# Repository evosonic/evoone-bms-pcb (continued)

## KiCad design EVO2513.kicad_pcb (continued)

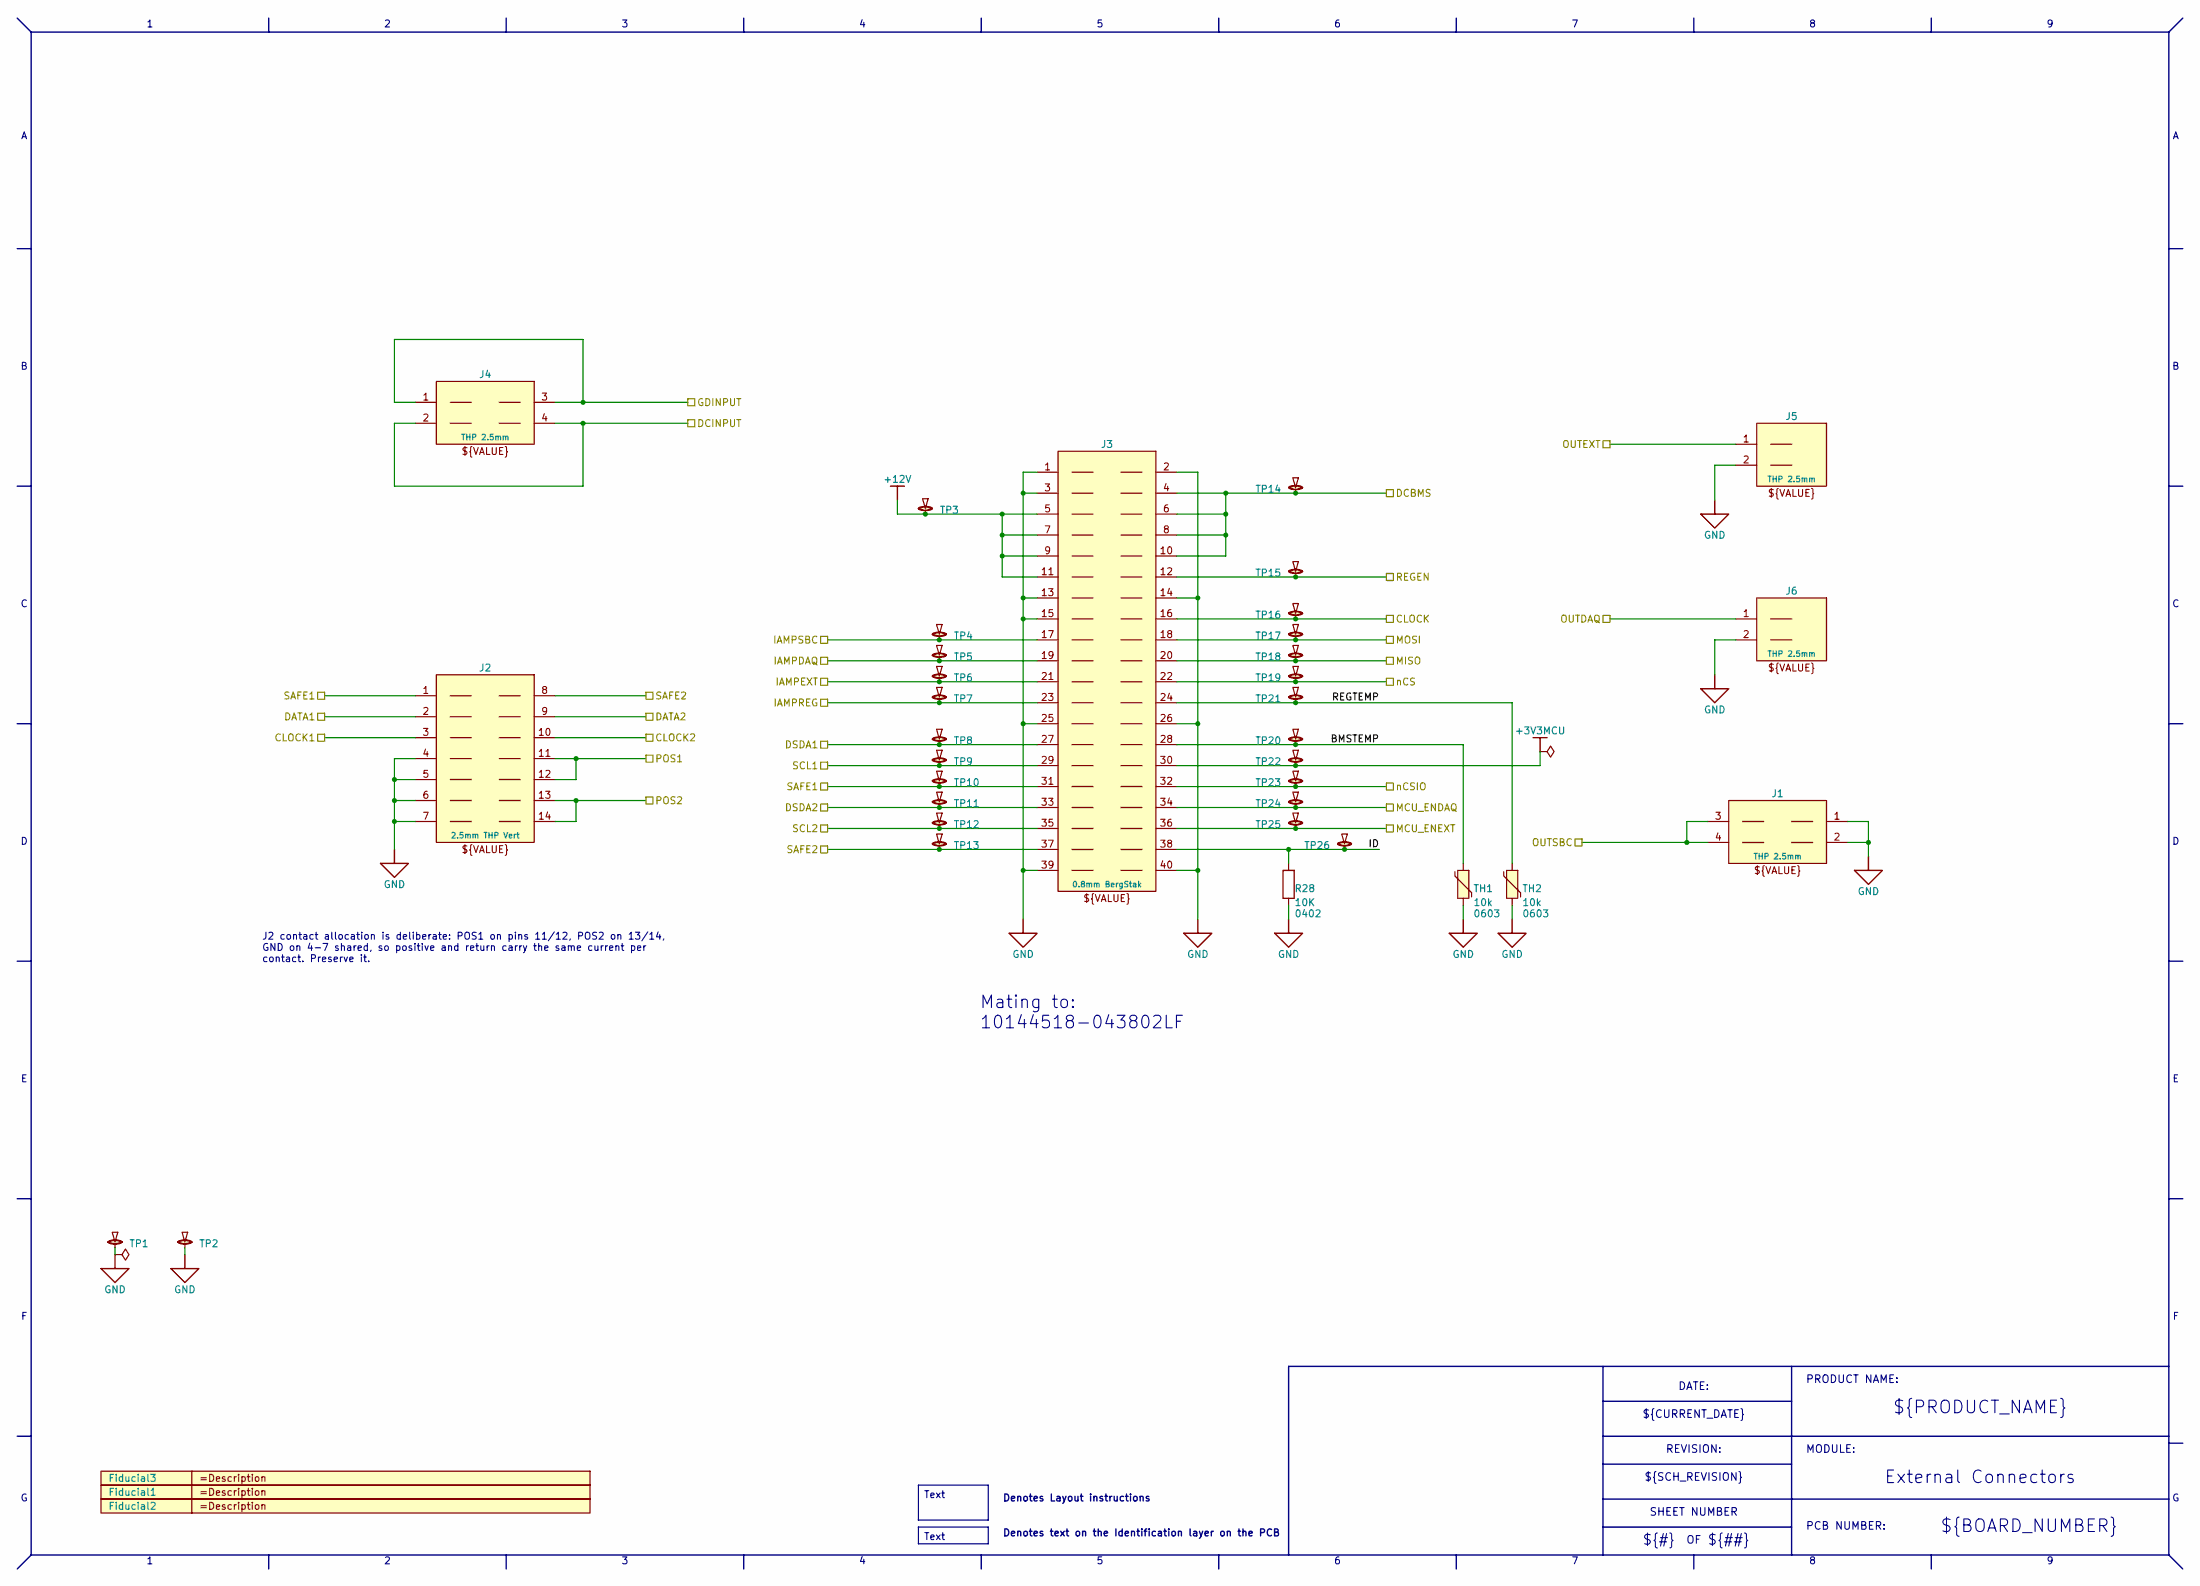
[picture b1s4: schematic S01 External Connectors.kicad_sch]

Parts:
Fiducial1, Fiducial2, Fiducial3: Fiducial; Fiducial-50
J1: 1053101204; Connector Molex 105310xx04 4POS 2.5mm THP; MANUFACTURER_PN 1053101204
J2: 1053101114; CONNECTOR MOLEX 1053101114 2.5MM THP; MANUFACTURER_PN 1053101114
J3: 10144517-043802LF; Connector Amphenol BergStak 10144517-043802LF 40-Pin Recept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; MANUFACTURER_PN 10144517-043802LF
J4: 1053102204; Connector Molex 105310xx04 4POS 2.5mm THP; MANUFACTURER_PN 1053102204
J5, J6: 1053091102; CONNECTOR MOLEX 1053091102 2POS 2.5MM THP; MANUFACTURER_PN 1053091102
R28: 10K; R_0402_1005Metric; MANUFACTURER_PN RC0402FR-0710KL
TH1, TH2: 10k; R_0603_1608Metric; MANUFACTURER_PN NCU18XH103E6SRB
TP1, TP2, TP3, TP4, TP5, TP6, TP7, TP8, TP9, TP10, TP11, TP12, TP13, TP14, TP15, TP16, TP17, TP18, TP19, TP20, TP21, TP22, TP23, TP24, TP25, TP26: POGO-1; TEST PIN 1-25mm SMD Pad (POGO-1)

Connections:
+3V3MCU: J3.30 (I/O), TP22.1 (1_1); also elsewhere on the board
+12V: J3.5 (I/O), J3.7 (I/O), J3.9 (I/O), J3.11 (I/O), TP3.1 (1_1); also elsewhere on the board
/CLOCK: J3.16 (I/O), TP16.1 (1_1); also elsewhere on the board
/CLOCK1: J2.3 (I/O); also elsewhere on the board
/CLOCK2: J2.10 (I/O); also elsewhere on the board
/DATA1: J2.2 (I/O); also elsewhere on the board
/DATA2: J2.9 (I/O); also elsewhere on the board
/DCBMS: J3.4 (I/O), J3.6 (I/O), J3.8 (I/O), J3.10 (I/O), TP14.1 (1_1); also elsewhere on the board
/DCINPUT: J4.2 (I/O), J4.4 (I/O); also elsewhere on the board
/DSDA1: J3.27 (I/O), TP8.1 (1_1); also elsewhere on the board
/DSDA2: J3.33 (I/O), TP11.1 (1_1); also elsewhere on the board
/GDINPUT: J4.1 (I/O), J4.3 (I/O); also elsewhere on the board
/IAMPDAQ: J3.19 (I/O), TP5.1 (1_1); also elsewhere on the board
/IAMPEXT: J3.21 (I/O), TP6.1 (1_1); also elsewhere on the board
/IAMPREG: J3.23 (I/O), TP7.1 (1_1); also elsewhere on the board
/IAMPSBC: J3.17 (I/O), TP4.1 (1_1); also elsewhere on the board
/MCU_ENDAQ: J3.34 (I/O), TP24.1 (1_1); also elsewhere on the board
/MCU_ENEXT: J3.36 (I/O), TP25.1 (1_1); also elsewhere on the board
/MISO: J3.20 (I/O), TP18.1 (1_1); also elsewhere on the board
/MOSI: J3.18 (I/O), TP17.1 (1_1); also elsewhere on the board
/OUTDAQ: J6.1 (I/O); also elsewhere on the board
/OUTEXT: J5.1 (I/O); also elsewhere on the board
/OUTSBC: J1.3 (I/O), J1.4 (I/O); also elsewhere on the board
/POS1: J2.11 (I/O), J2.12 (I/O); also elsewhere on the board
/POS2: J2.13 (I/O), J2.14 (I/O); also elsewhere on the board
/REGEN: J3.12 (I/O), TP15.1 (1_1); also elsewhere on the board
/S01 External Connectors/BMSTEMP: J3.28 (I/O), TH1.2, TP20.1 (1_1)
/S01 External Connectors/ID: J3.38 (I/O), R28.2, TP26.1 (1_1)
/S01 External Connectors/REGTEMP: J3.24 (I/O), TH2.2, TP21.1 (1_1)
/SAFE1: J2.1 (I/O), J3.31 (I/O), TP10.1 (1_1); also elsewhere on the board
/SAFE2: J2.8 (I/O), J3.37 (I/O), TP13.1 (1_1); also elsewhere on the board
/SCL1: J3.29 (I/O), TP9.1 (1_1); also elsewhere on the board
/SCL2: J3.35 (I/O), TP12.1 (1_1); also elsewhere on the board
/nCS: J3.22 (I/O), TP19.1 (1_1); also elsewhere on the board
/nCSIO: J3.32 (I/O), TP23.1 (1_1); also elsewhere on the board
GND: J1.1 (I/O), J1.2 (I/O), J2.4 (I/O), J2.5 (I/O), J2.6 (I/O), J2.7 (I/O), J3.1 (I/O), J3.2 (I/O), J3.3 (I/O), J3.13 (I/O), J3.14 (I/O), J3.15 (I/O), J3.25 (I/O), J3.26 (I/O), J3.39 (I/O), J3.40 (I/O), J5.2 (I/O), J6.2 (I/O), R28.1, TH1.1, TH2.1, TP1.1 (1_1), TP2.1 (1_1); also elsewhere on the board

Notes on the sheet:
Denotes Layout instructions
PCB NUMBER:
${BOARD_NUMBER}
REVISION:
${#}
PRODUCT NAME:
J2 contact allocation is deliberate: POS1 on pins 11/12, POS2 on 13/14, GND on 4-7 shared, so positive and return carry the same current per contact. Preserve it.
${PRODUCT_NAME}
SHEET NUMBER
${SCH_REVISION}
MODULE:
DATE:
External Connectors
${CURRENT_DATE}
${##}
Denotes text on the Identification layer on the PCB
Mating to: 10144518-043802LF
Text

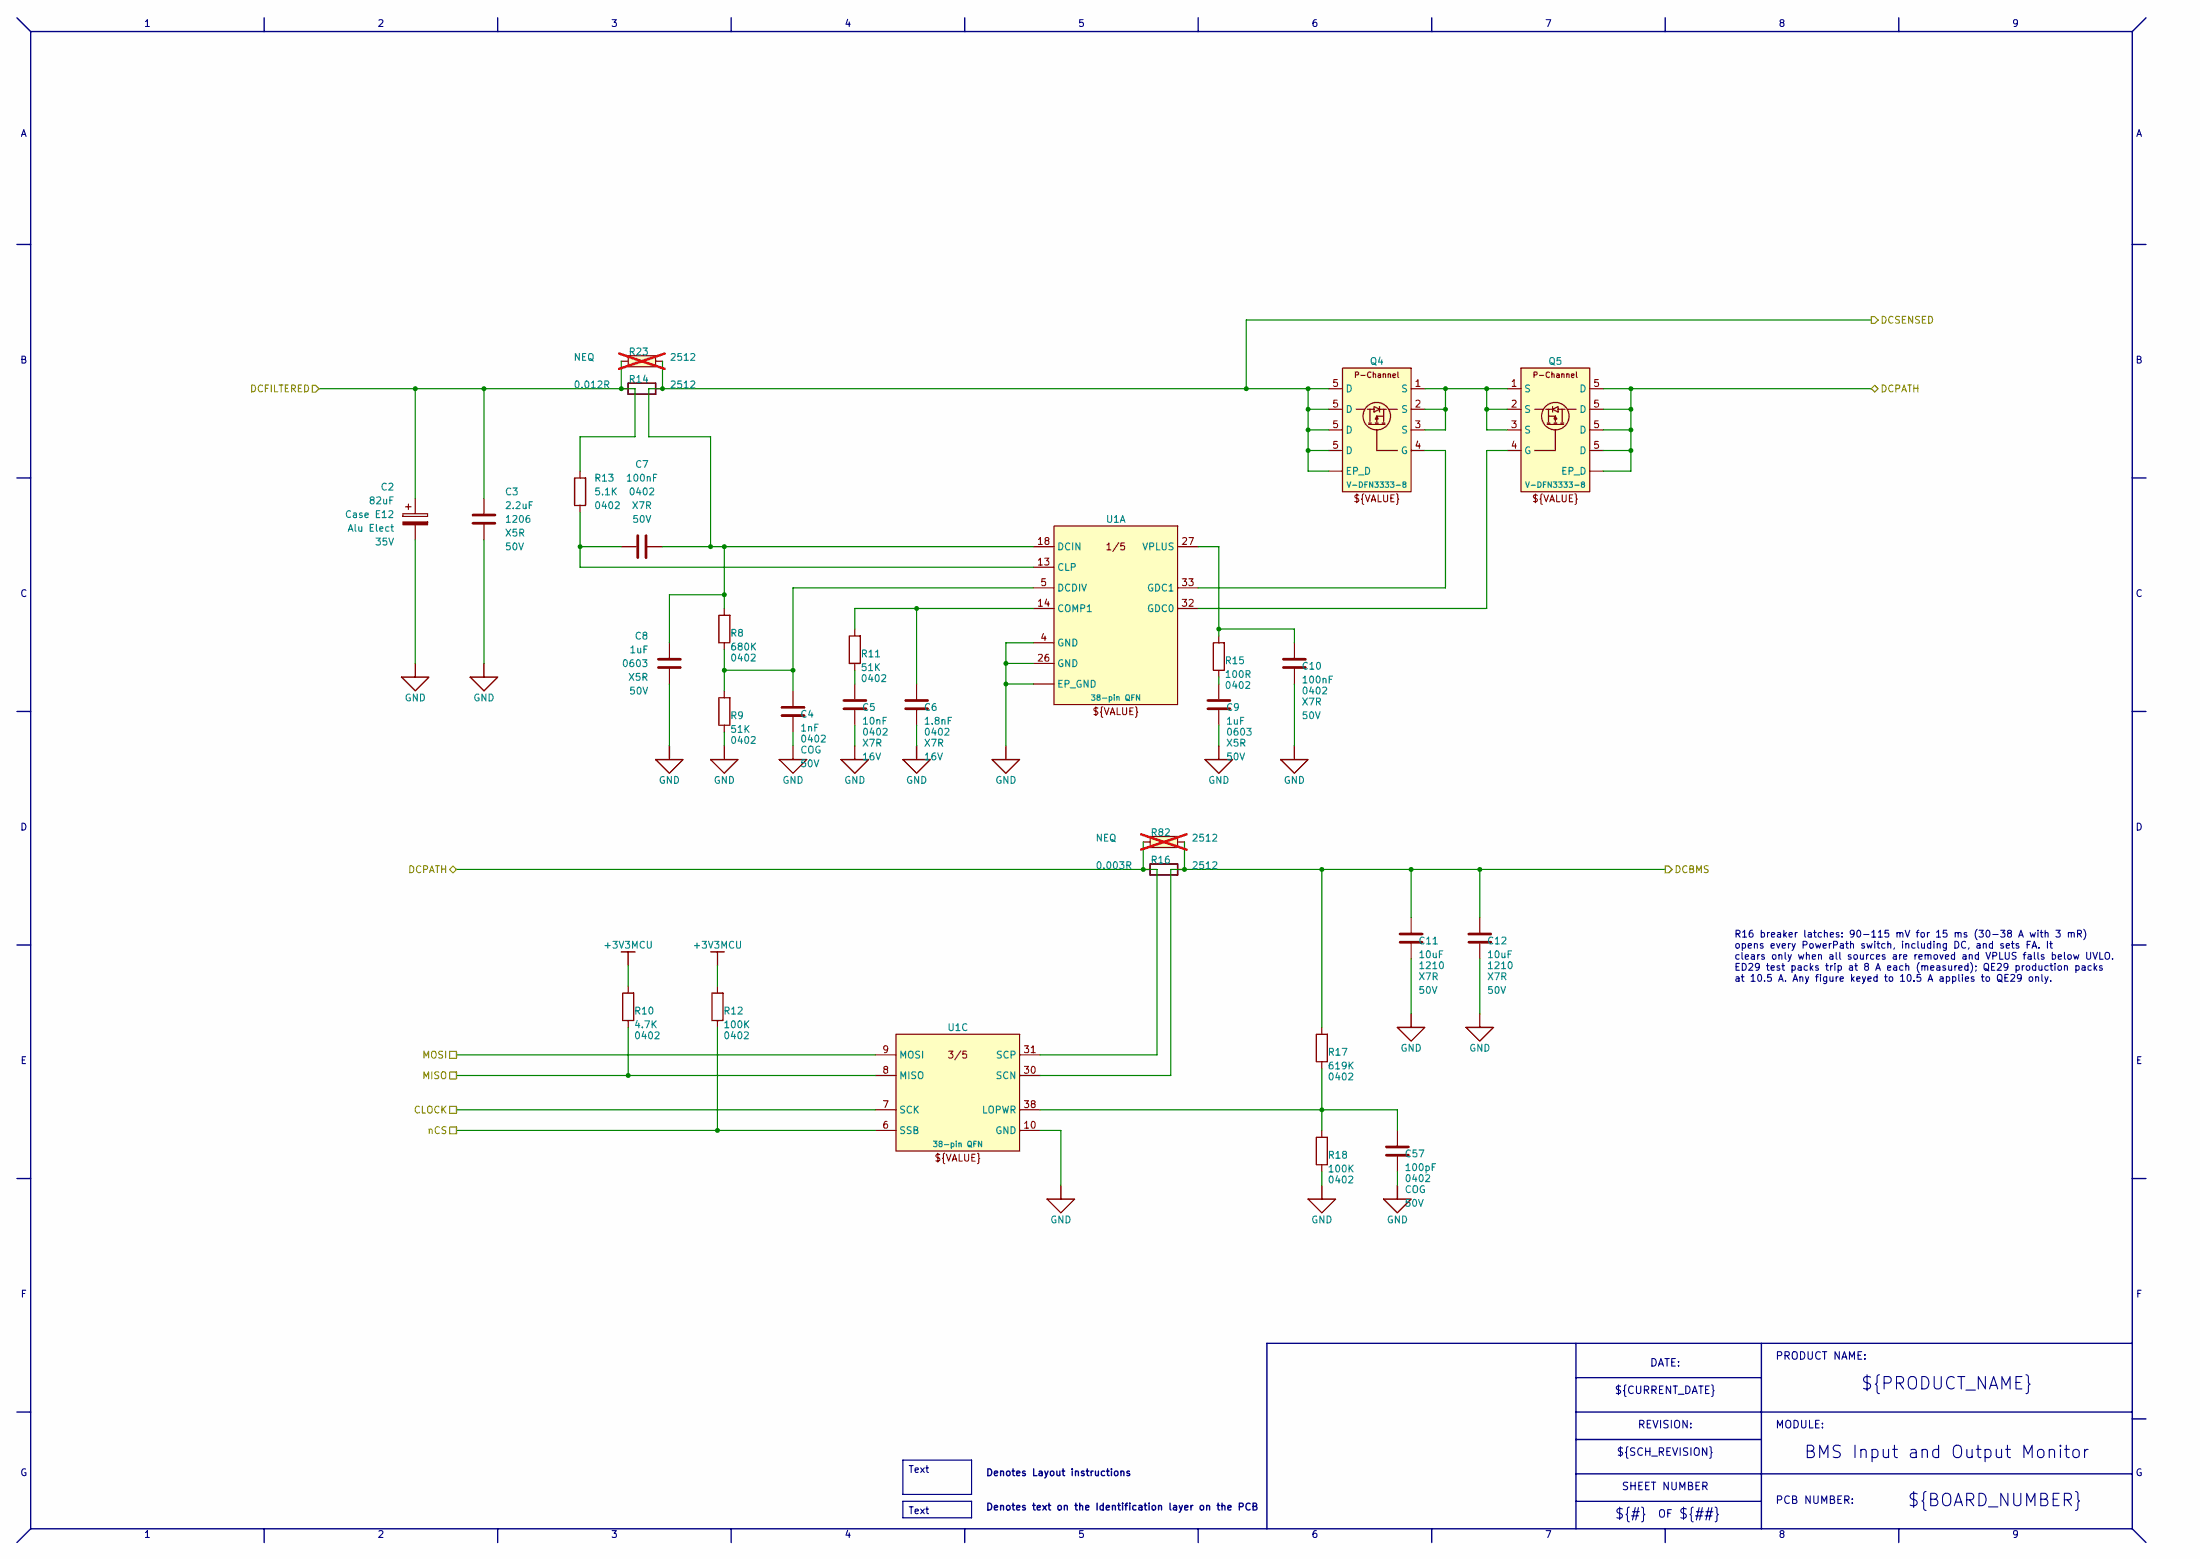
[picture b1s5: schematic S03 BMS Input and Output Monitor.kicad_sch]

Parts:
C2: 82uF; CAP Panasonic CASE-E12; VOLTAGE 35V; MANUFACTURER_PN 35SVPF82M
C3: 2.2uF; C_1206_3216Metric; VOLTAGE 50V; MANUFACTURER_PN CC1206KKX5R9BB225
C4: 1nF; C_0402_1005Metric; VOLTAGE 50V; MANUFACTURER_PN AC0402JRNPO9BN102
C5: 10nF; C_0402_1005Metric; VOLTAGE 16V; MANUFACTURER_PN GRM155R71C103KA01D
C6: 1.8nF; C_0402_1005Metric; VOLTAGE 16V; MANUFACTURER_PN CC0402KRX7R9BB182
C7, C10: 100nF; C_0402_1005Metric; VOLTAGE 50V; MANUFACTURER_PN CC0402KPX7R9BB104
C8, C9: 1uF; C_0603_1608Metric; VOLTAGE 50V; MANUFACTURER_PN CL10A105KB8NNNC
C11, C12: 10uF; C_1210_3225Metric; VOLTAGE 50V; MANUFACTURER_PN UMK325AB7106KMHP
C57: 100pF; C_0402_1005Metric; VOLTAGE 50V; MANUFACTURER_PN CC0402JRNPO9BN101
Q4, Q5: DMP3007SCG-13; Diodes_PowerDI3333-8; MANUFACTURER_PN DMP3007SCG-13
R8: 680K; R_0402_1005Metric; MANUFACTURER_PN RC0402FR-07680KL
R9, R11: 51K; R_0402_1005Metric; MANUFACTURER_PN RC0402FR-0751KL
R10: 4.7K; R_0402_1005Metric; MANUFACTURER_PN RC0402FR-134K7L
R12, R18: 100K; R_0402_1005Metric; MANUFACTURER_PN RC0402FR-07100KL
R13: 5.1K; R_0402_1005Metric; MANUFACTURER_PN RC0402FR-075K1L
R14: 0.012R; R_2512_6332Metric; MANUFACTURER_PN PA2512FKE7W0R012E
R15: 100R; R_0402_1005Metric; MANUFACTURER_PN RC0402FR-07100RL
R16: 0.003R; R_2512_6332Metric; MANUFACTURER_PN CRE2512-FZ-R003E-3
R17: 619K; R_0402_1005Metric; MANUFACTURER_PN RC0402FR-07619KL
R23, R82: NEQ; R_2512_6332Metric; MANUFACTURER_PN Res 2512; not fitted
U1: LTC1960; QFN B5x7 P0-5 38-Pin EP; MANUFACTURER_PN LTC1960CUHF#PBF

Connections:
+3V3MCU: R10.2, R12.2; also elsewhere on the board
/CLOCK: U1.7 (SCK); also elsewhere on the board
/DCBMS: C11.2, C12.2, R16.2, R17.2, R82.2, U1.30 (SCN); also elsewhere on the board
/DCFILTERED: C2.1, C3.2, R13.2, R14.1, R23.1; also elsewhere on the board
/DCPATH: Q5.5 (EP_D), R16.1, R82.1, U1.31 (SCP); also elsewhere on the board
/DCSENSED: C7.2, C8.2, Q4.5 (EP_D), R8.2, R14.2, R23.2, U1.18 (DCIN); also elsewhere on the board
/MISO: R10.1, U1.8 (MISO); also elsewhere on the board
/MOSI: U1.9 (MOSI); also elsewhere on the board
/nCS: R12.1, U1.6 (SSB); also elsewhere on the board
GND: C2.2, C3.1, C4.1, C5.1, C6.1, C8.1, C9.1, C10.1, C11.1, C12.1, C57.1, R9.1, R18.1, U1.4 (GND), U1.10 (GND), U1.26 (GND), U1.39 (EP_GND); also elsewhere on the board
unnamed: C5.2, R11.1
unnamed: C9.2, R15.1
unnamed: Q4.4 (G), U1.33 (GDC1)
unnamed: Q4.1 (S), Q4.2 (S), Q4.3 (S), Q5.1 (S), Q5.2 (S), Q5.3 (S)
unnamed: Q5.4 (G), U1.32 (GDC0)
unnamed: C7.1, R13.1, U1.13 (CLP)
unnamed: C6.2, R11.2, U1.14 (COMP1)
unnamed: C4.2, R8.1, R9.2, U1.5 (DCDIV)
unnamed: C10.2, R15.2, U1.27 (VPLUS)
unnamed: C57.2, R17.1, R18.2, U1.38 (LOPWR)

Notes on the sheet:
${#}
PCB NUMBER:
SHEET NUMBER
MODULE:
${BOARD_NUMBER}
DATE:
${PRODUCT_NAME}
R16 breaker latches: 90-115 mV for 15 ms (30-38 A with 3 mR) opens every PowerPath switch, including DC, and sets FA. It clears only when all sources are removed and VPLUS falls below UVLO. ED29 test packs trip at 8 A each (measured); QE29 production packs at 10.5 A. Any figure keyed to 10.5 A appl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
${##}
Denotes text on the Identification layer on the PCB
PRODUCT NAME:
REVISION:
BMS Input and Output Monitor
Denotes Layout instructions
${CURRENT_DATE}
${SCH_REVISION}
Text

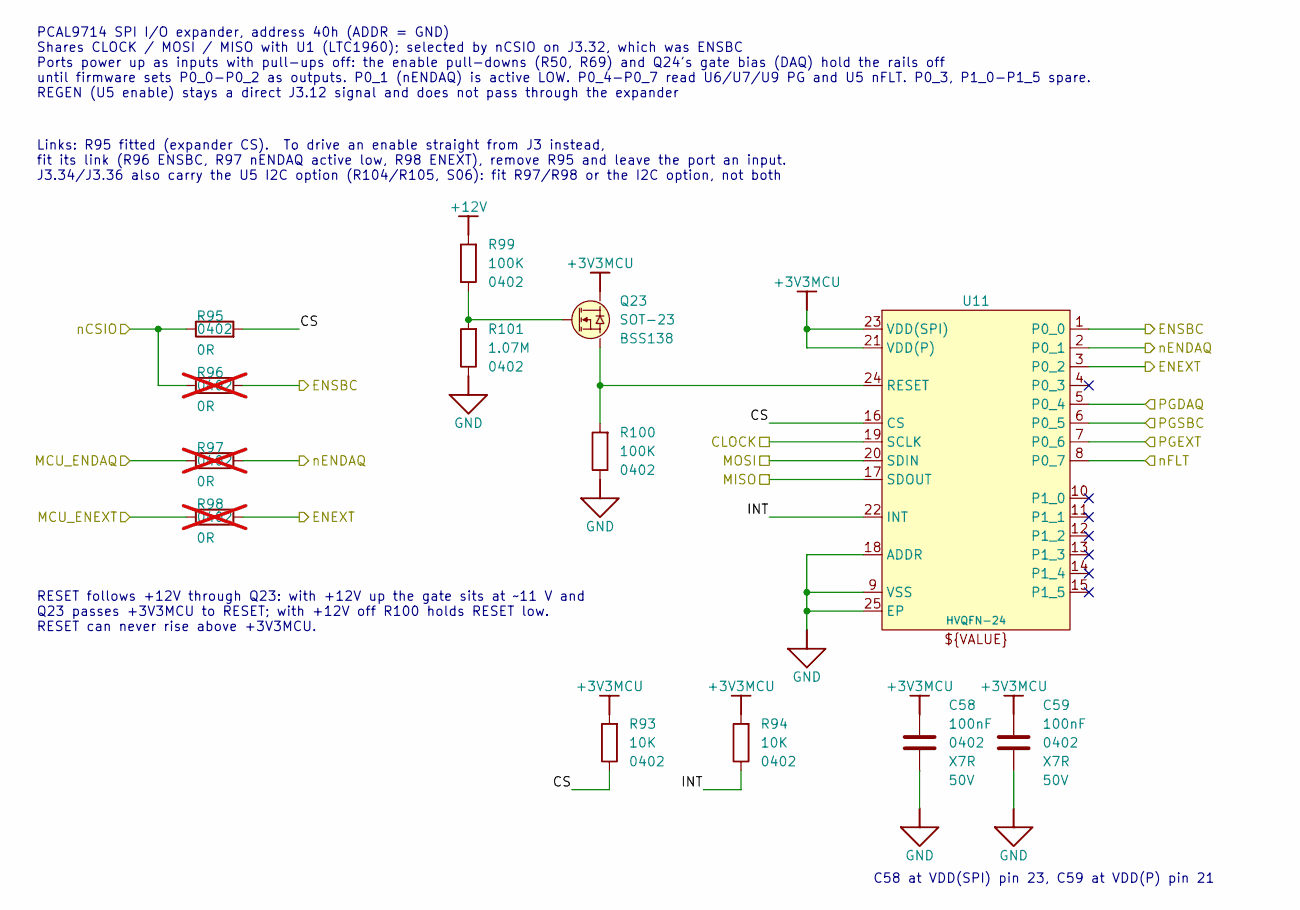
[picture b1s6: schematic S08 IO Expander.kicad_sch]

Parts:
C58, C59: 100nF; C_0402_1005Metric; VOLTAGE 50V; MANUFACTURER_PN CC0402KPX7R9BB104
Q23: BSS138; SOT-23; MANUFACTURER_PN BSS138
R93, R94: 10K; R_0402_1005Metric; MANUFACTURER_PN RC0402FR-0710KL
R95: 0R; R_0402_1005Metric; MANUFACTURER_PN RC0402JR-070RL
R96, R97, R98: 0R; R_0402_1005Metric; MANUFACTURER_PN RC0402JR-070RL; not fitted
R99, R100: 100K; R_0402_1005Metric; MANUFACTURER_PN RC0402FR-07100KL
R101: 1.07M; R_0402_1005Metric; MANUFACTURER_PN RC0402FR-071M07L
U11: PCAL9714; HVQFN-24-1EP_4x4mm_P0.5mm_EP2.6x2.6mm; MANUFACTURER_PN PCAL9714HNMP

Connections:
+3V3MCU: C58.2, C59.2, Q23.3 (D), R93.2, R94.2, U11.21 (VDD(P)), U11.23 (VDD(SPI)); also elsewhere on the board
+12V: R99.2; also elsewhere on the board
/CLOCK: U11.19 (SCLK); also elsewhere on the board
/ENEXT: R98.2, U11.3 (P0_2); also elsewhere on the board
/ENSBC: R96.2, U11.1 (P0_0); also elsewhere on the board
/MCU_ENDAQ: R97.1; also elsewhere on the board
/MCU_ENEXT: R98.1; also elsewhere on the board
/MISO: U11.17 (SDOUT); also elsewhere on the board
/MOSI: U11.20 (SDIN); also elsewhere on the board
/PGDAQ: U11.5 (P0_4); also elsewhere on the board
/PGEXT: U11.7 (P0_6); also elsewhere on the board
/PGSBC: U11.6 (P0_5); also elsewhere on the board
/S08 IO Expander/CS: R93.1, R95.2, U11.16 (CS)
/S08 IO Expander/INT: R94.1, U11.22 (INT)
/nCSIO: R95.1, R96.1; also elsewhere on the board
/nENDAQ: R97.2, U11.2 (P0_1); also elsewhere on the board
/nFLT: U11.8 (P0_7); also elsewhere on the board
GND: C58.1, C59.1, R100.1, R101.1, U11.9 (VSS), U11.18 (ADDR), U11.25 (EP); also elsewhere on the board
unnamed: Q23.1 (G), R99.1, R101.2
unnamed: Q23.2 (S), R100.2, U11.24 (RESET)

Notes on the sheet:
Links: R95 fitted (expander CS). To drive an enable straight from J3 instead, fit its link (R96 ENSBC, R97 nENDAQ active low, R98 ENEXT), remove R95 and leave the port an input. J3.34/J3.36 also carry the U5 I2C option (R104/R105, S06): fit R97/R98 or the I2C option, not both
RESET follows +12V through Q23: with +12V up the gate sits at ~11 V and Q23 passes +3V3MCU to RESET; with +12V off R100 holds RESET low. RESET can never rise above +3V3MCU.
C58 at VDD(SPI) pin 23, C59 at VDD(P) pin 21
PCAL9714 SPI I/O expander, address 40h (ADDR = GND) Shares CLOCK / MOSI / MISO with U1 (LTC1960); selected by nCSIO on J3.32, which was ENSBC Ports power up as inputs with pull-ups off: the enable pull-downs (R50, R69) and Q24's gate bias (DAQ) hold the rails off until firmware sets P0_0-P0_2 as ou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

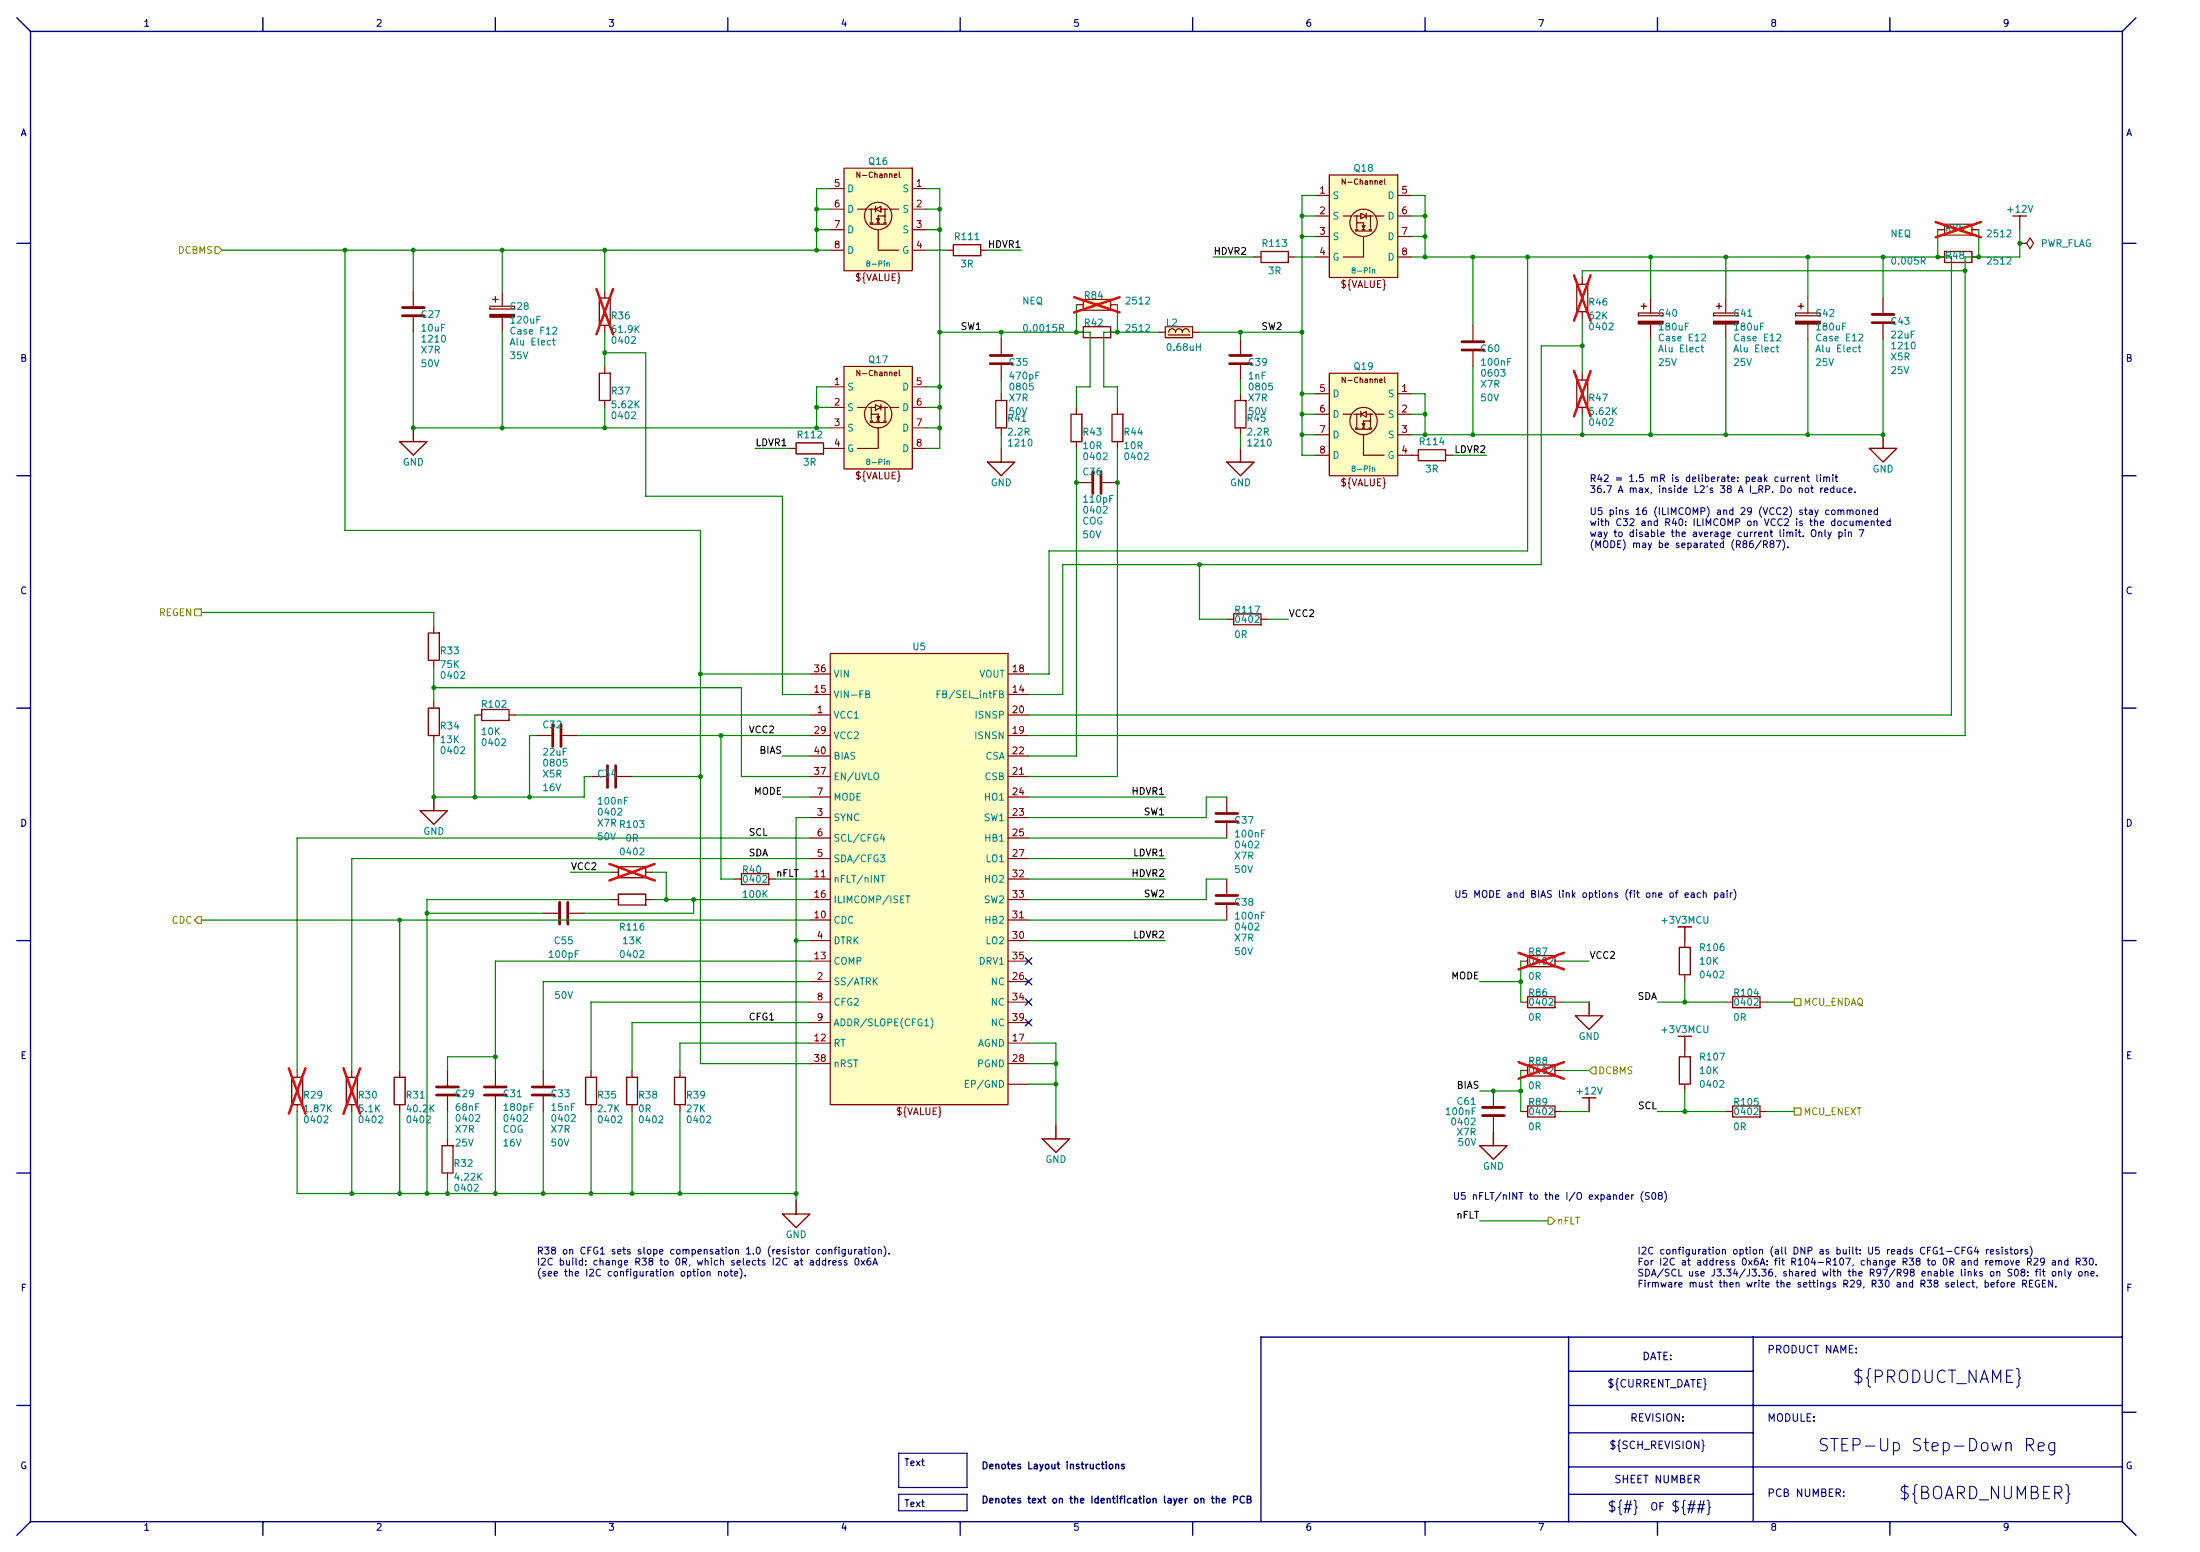
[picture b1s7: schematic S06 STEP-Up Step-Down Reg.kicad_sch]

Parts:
C27: 10uF; C_1210_3225Metric; VOLTAGE 50V; MANUFACTURER_PN UMK325AB7106KMHP
C28: 120uF; CAP Panasonic CASE-F12; VOLTAGE 35V; MANUFACTURER_PN 35SVPF120M
C29: 68nF; C_0402_1005Metric; VOLTAGE 25V; MANUFACTURER_PN CC0402KRX7R8BB683
C31: 180pF; C_0402_1005Metric; VOLTAGE 16V; MANUFACTURER_PN CC0402JRNPO9BN181
C32: 22uF; C_0805_2012Metric; VOLTAGE 16V; MANUFACTURER_PN GRM219R61C226ME15L
C33: 15nF; C_0402_1005Metric; VOLTAGE 50V; MANUFACTURER_PN CC0402KRX7R9BB153
C34, C37, C38, C61: 100nF; C_0402_1005Metric; VOLTAGE 50V; MANUFACTURER_PN CC0402KPX7R9BB104
C35: 470pF; C_0805_2012Metric; VOLTAGE 50V; MANUFACTURER_PN CC0805KRX7R9BB471
C36: 110pF; C_0402_1005Metric; VOLTAGE 50V; MANUFACTURER_PN CC0402JRNPO9BN111
C39: 1nF; C_0805_2012Metric; VOLTAGE 50V; MANUFACTURER_PN CC0805KPX7R9BB102
C40, C41, C42: 180uF; CAP Panasonic CASE-E12; VOLTAGE 25V; MANUFACTURER_PN 25SVPF180M
C43: 22uF; C_1210_3225Metric; VOLTAGE 25V; MANUFACTURER_PN CL32A226KAJNNWE
C55: 100pF; C_0402_1005Metric; VOLTAGE 50V; MANUFACTURER_PN CC0402JRNPO9BN101
C60: 100nF; C_0603_1608Metric; VOLTAGE 50V; MANUFACTURER_PN CC0603KRX7R9BB104
L2: 0.68uH; IND COILCRAFT XAL8080; MANUFACTURER_PN 744393580068
Q16, Q19: IAUCN04S7L019; Infineon_PG-TDSON-8-33_5.48x5.15mm_P1.27mm; MANUFACTURER_PN IAUCN04S7L019ATMA1
Q17: IAUCN04S7L028; Infineon_PG-TDSON-8-33_5.48x5.15mm_P1.27mm; MANUFACTURER_PN IAUCN04S7L028ATMA1
Q18: CSD17304Q3; Power CSD17304Q3-8 B3.3 x 3.3 P0.65 Tab 8-Pin EP1.75 x 2.45; MANUFACTURER_PN CSD17304Q3
R29: 1.87K; R_0402_1005Metric; MANUFACTURER_PN RC0402FR-071K87L; not fitted
R30: 5.1K; R_0402_1005Metric; MANUFACTURER_PN RC0402FR-075K1L; not fitted
R31: 40.2K; R_0402_1005Metric; MANUFACTURER_PN RC0402FR-1340K2L
R32: 4.22K; R_0402_1005Metric; MANUFACTURER_PN RC0402FR-074K22L
R33: 75K; R_0402_1005Metric; MANUFACTURER_PN RC0402FR-0775KL
R34: 13K; R_0402_1005Metric; MANUFACTURER_PN RC0402FR-0713KL
R35: 2.7K; R_0402_1005Metric; MANUFACTURER_PN RC0402FR-072K7L
R36: 61.9K; R_0402_1005Metric; MANUFACTURER_PN RC0402FR-0761K9L; not fitted
R37: 5.62K; R_0402_1005Metric; MANUFACTURER_PN RC0402FR-075K62L
R38, R86, R89, R104, R105, R117: 0R; R_0402_1005Metric; MANUFACTURER_PN RC0402JR-070RL
R39: 27K; R_0402_1005Metric; MANUFACTURER_PN RC0402FR-0727KL
R40: 100K; R_0402_1005Metric; MANUFACTURER_PN RC0402FR-07100KL
R41, R45: 2.2R; R_1210_3225Metric; MANUFACTURER_PN AC1210FR-072R2L
R42: 0.0015R; R_2512_6332Metric; MANUFACTURER_PN WPB2512RL1M50FYR
R43, R44: 10R; R_0402_1005Metric; MANUFACTURER_PN RC0402FR-0710RL
R46: 62K; R_0402_1005Metric; MANUFACTURER_PN RC0402FR-0762KL; not fitted
R47: 5.62K; R_0402_1005Metric; MANUFACTURER_PN RC0402FR-075K62L; not fitted
R48: 0.005R; R_2512_6332Metric; MANUFACTURER_PN CRE2512-FZ-R005E-3
R84, R85: NEQ; R_2512_6332Metric; MANUFACTURER_PN Res 2512; not fitted
R87, R88, R103: 0R; R_0402_1005Metric; MANUFACTURER_PN RC0402JR-070RL; not fitted
R102, R106, R107: 10K; R_0402_1005Metric; MANUFACTURER_PN RC0402FR-0710KL
R111, R112, R113, R114: 3R; R_0603_1608Metric; MANUFACTURER_PN RC0603FR-073RL
R116: 13K; R_0402_1005Metric; MANUFACTURER_PN RC0402JR-070RL
U5: LM51772RHAR; QFN B6x6 P0-5 40-Pin EP; MANUFACTURER_PN LM51772RHAR

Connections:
+3V3MCU: R106.2, R107.2; also elsewhere on the board
+12V: R46.2, R48.1, R85.1, R89.2, U5.19 (ISNSN); also elsewhere on the board
/CDC: R31.2, U5.10 (CDC); also elsewhere on the board
/DCBMS: C27.2, C28.1, C34.1, Q16.5 (D), Q16.6 (D), Q16.7 (D), Q16.8 (D), R36.2, R88.2, U5.36 (VIN), U5.38 (nRST); also elsewhere on the board
/MCU_ENDAQ: R104.2; also elsewhere on the board
/MCU_ENEXT: R105.2; also elsewhere on the board
/REGEN: R33.2; also elsewhere on the board
/S06 STEP-Up Step-Down Reg/BIAS: C61.1, R88.1, R89.1, U5.40 (BIAS)
/S06 STEP-Up Step-Down Reg/CFG1: R38.2, U5.9 (ADDR/SLOPE(CFG1))
/S06 STEP-Up Step-Down Reg/HDVR1: R111.2, U5.24 (HO1)
/S06 STEP-Up Step-Down Reg/HDVR2: R113.1, U5.32 (HO2)
/S06 STEP-Up Step-Down Reg/LDVR1: R112.1, U5.27 (LO1)
/S06 STEP-Up Step-Down Reg/LDVR2: R114.2, U5.30 (LO2)
/S06 STEP-Up Step-Down Reg/MODE: R86.1, R87.1, U5.7 (MODE)
/S06 STEP-Up Step-Down Reg/SCL: R29.2, R105.1, R107.1, U5.6 (SCL/CFG4)
/S06 STEP-Up Step-Down Reg/SDA: R30.2, R104.1, R106.1, U5.5 (SDA/CFG3)
/S06 STEP-Up Step-Down Reg/SW1: C35.2, C37.2, Q16.1 (S), Q16.2 (S), Q16.3 (S), Q17.5 (D), Q17.6 (D), Q17.7 (D), Q17.8 (D), R42.1, R43.2, R84.1, U5.23 (SW1)
/S06 STEP-Up Step-Down Reg/SW2: C38.2, C39.2, L2.2, Q18.1 (S), Q18.2 (S), Q18.3 (S), Q19.5 (D), Q19.6 (D), Q19.7 (D), Q19.8 (D), U5.33 (SW2)
/S06 STEP-Up Step-Down Reg/VCC2: C32.2, R40.1, R87.2, R103.2, R117.2, U5.29 (VCC2)
/nFLT: R40.2, U5.11 (nFLT/nINT); also elsewhere on the board
GND: C27.1, C28.2, C31.1, C32.1, C33.1, C34.2, C40.2, C41.2, C42.2, C43.1, C55.2, C60.1, C61.2, Q17.1 (S), Q17.2 (S), Q17.3 (S), Q19.1 (S), Q19.2 (S), Q19.3 (S), R29.1, R30.1, R31.1, R32.1, R34.1, R35.1, R37.1, R38.1, R39.1, R41.1, R45.1, R47.1, R86.2, R102.1, R116.1, U5.3 (SYNC), U5.4 (DTRK), U5.17 (AGND), U5.28 (PGND), U5.41 (EP/GND); also elsewhere on the board
unnamed: C29.1, R32.2
unnamed: C35.1, R41.2
unnamed: C39.1, R45.2
unnamed: L2.1, R42.2, R44.2, R84.2
unnamed: Q16.4 (G), R111.1
unnamed: Q17.4 (G), R112.2
unnamed: Q18.4 (G), R113.2
unnamed: Q19.4 (G), R114.1
unnamed: R35.2, U5.8 (CFG2)
unnamed: C29.2, C31.2, U5.13 (COMP)
unnamed: C36.1, R43.1, U5.22 (CSA)
unnamed: C36.2, R44.1, U5.21 (CSB)
unnamed: R33.1, R34.2, U5.37 (EN/UVLO)
unnamed: R46.1, R47.2, R117.1, U5.14 (FB/SEL_intFB)
unnamed: C37.1, U5.25 (HB1)
unnamed: C38.1, U5.31 (HB2)
unnamed: C55.1, R103.1, R116.2, U5.16 (ILIMCOMP/ISET)
unnamed: C40.1, C41.1, C42.1, C43.2, C60.2, Q18.5 (D), Q18.6 (D), Q18.7 (D), Q18.8 (D), R48.2, R85.2, U5.18 (VOUT), U5.20 (ISNSP)
unnamed: R39.2, U5.12 (RT)
unnamed: C33.2, U5.2 (SS/ATRK)
unnamed: R102.2, U5.1 (VCC1)
unnamed: R36.1, R37.2, U5.15 (VIN-FB)

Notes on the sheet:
DATE:
PCB NUMBER:
U5 nFLT/nINT to the I/O expander (S08)
Denotes text on the Identification layer on the PCB
SHEET NUMBER
PRODUCT NAME:
REVISION:
${##}
${BOARD_NUMBER}
I2C configuration option (all DNP as built: U5 reads CFG1-CFG4 resistors) For I2C at address 0x6A: fit R104-R107, change R38 to 0R and remove R29 and R30. SDA/SCL use J3.34/J3.36, shared with the R97/R98 enable links on S08: fit only one. Firmware must then write the settings R29, R30 and R38 selec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
R38 on CFG1 sets slope compensation 1.0 (resistor configuration). I2C build: change R38 to 0R, which selects I2C at address 0x6A (see the I2C configuration option note).
${PRODUCT_NAME}
Denotes Layout instructions
${CURRENT_DATE}
MODULE:
${SCH_REVISION}
STEP-Up Step-Down Reg
U5 MODE and BIAS link options (fit one of each pair)
R42 = 1.5 mR is deliberate: peak current limit 36.7 A max, inside L2's 38 A I_RP. Do not reduce. U5 pins 16 (ILIMCOMP) and 29 (VCC2) stay commoned with C32 and R40: ILIMCOMP on VCC2 is the documented way to disable the average current limit. Only pin 7 (MODE) may be separated (R86/R87).
${#}
Text
